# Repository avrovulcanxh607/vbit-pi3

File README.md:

# vbit-pi3
Teletext inserter board for the Raspberry Pi

Code available at https://github.com/peterkvt80/vbit-py<br>
Instructions and other details available at https://www.nathanmediaservices.co.uk/vbit-pi/

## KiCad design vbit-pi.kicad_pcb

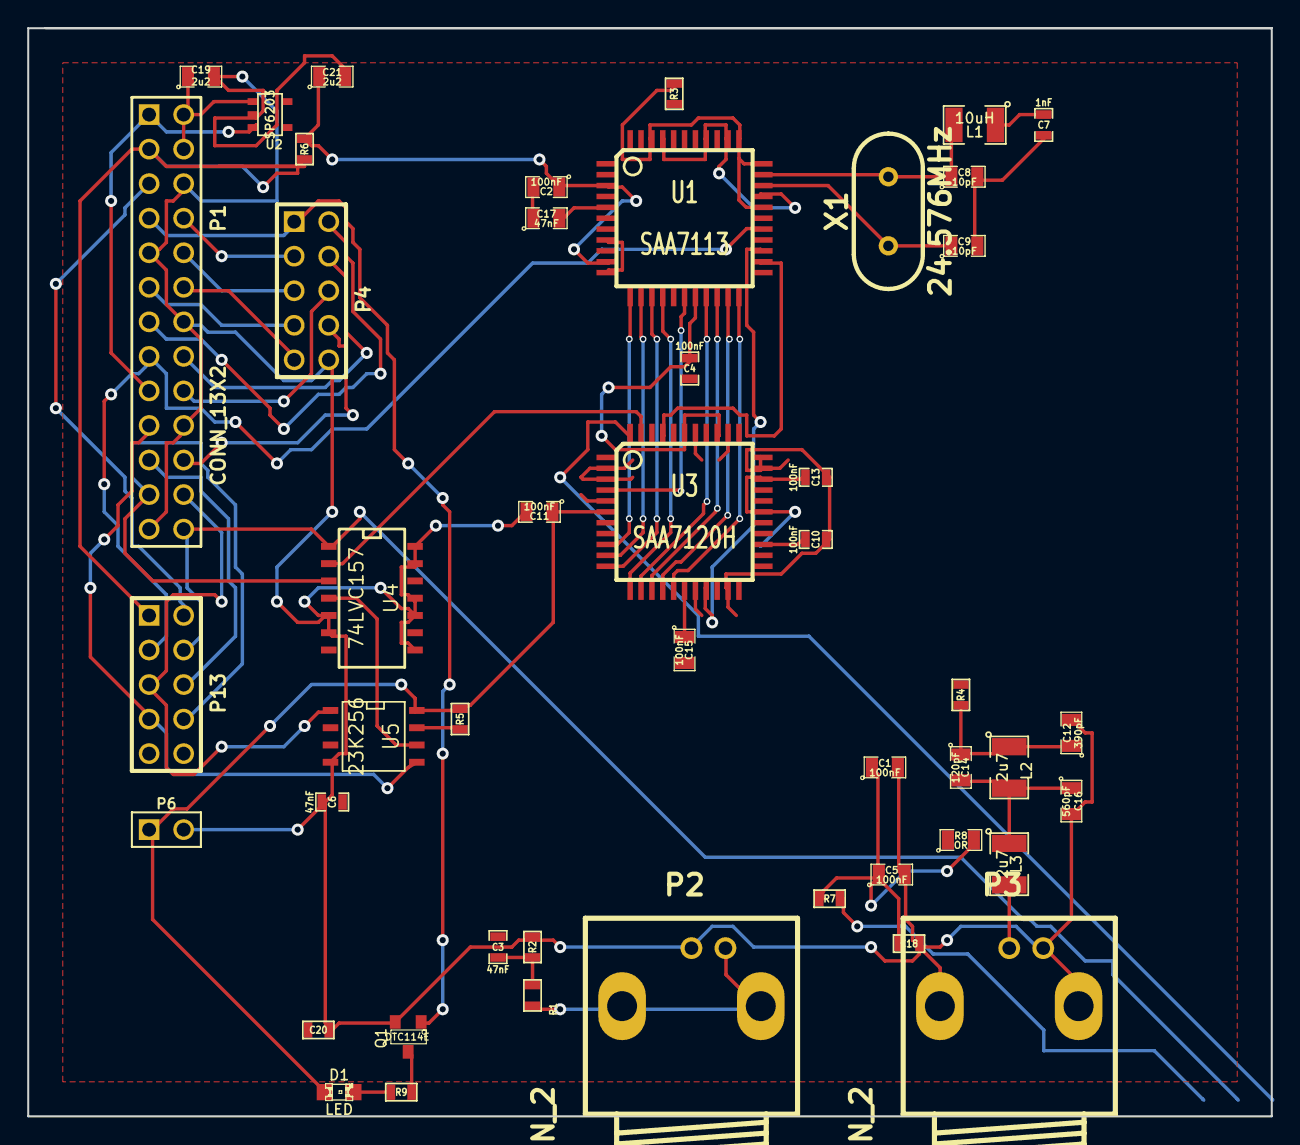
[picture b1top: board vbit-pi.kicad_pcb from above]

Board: 2 copper layers, 91.4 x 80.0 mm, 47 parts (0 on the bottom side), 51 nets.

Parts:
C1, C2, C5, C11, C15: 100nF; SM0805
C3, C6: 47nF; SM0603_Capa
C4, C10, C13: 100nF; SM0603_Capa
C7: 1nF; SM0603_Capa
C8, C9: 10pF; SM0805
C12: 390pF; SM0805
C14: 120pF; SM0805
C16: 560pF; SM0805
C17: 47nF; SM0805
C18: 100nF; SM0603
C19, C21: 2u2; SM0805
C20: 10nF; SM0603
D1: LED; LED-0805
L1: 10uH; SM1210
L2, L3: 2u7; SM1210
P1: CONN_13X2; pin_array_13x2
P2, P3: CONN_2; BNC_Socket_TYCO-AMP_RevA_Date21Jun2010
P4, P13: CONN_5X2; PIN_ARRAY_5x2
P6: CONN_2; PIN_ARRAY_2X1
Q1: DTC114E; SOT23
R1: 18R; SM0603
R2: 56R; SM0603
R3: 1k; SM0603
R4: 8R2; SM0603
R5: 47k; SM0603
R6, R7: 3k3; SM0603
R8: OR; SM0805
R9: 220R; SM0603
U1: SAA7113; TQFP44
U2: SP6203; SOT23-5
U3: SAA7120H; TQFP44
U4: 74LVC157; SO14N
U5: 23K256; SO8N
X1: 24.576MHz; HC-49V

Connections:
3V3 Power: P1.1, P1.17, U2.3
5V Power: C19.1, P1.2, P1.4, U2.1
+3.3V: C1.1, C2.1, C4.1, C5.1, C10.1, C11.1, C13.1, C15.1, C18.1, C21.1, D1.1, P6.1, R3.2, R5.1, R6.1, R7.1, R8.2, U1.3, U1.10, U1.18, U1.29, U1.33, U1.34, U1.42, U3.6, U3.17, U3.25, U3.28, U3.31, U3.36, U3.39, U3.40, U5.8
/DVID0: U1.22, U3.16
/DVID1: U1.21, U3.15
/DVID2: U1.20, U3.14
/DVID3: U1.19, U3.13
/DVID4: U1.15, U3.12
/DVID5: U1.14, U3.11
/DVID6: U1.13, U3.10
/DVID7: U1.12, U3.9
/LLC: U1.17, U3.4
/RTC: U1.25, U3.19
CSN: P1.24, P13.5, U5.1
FLD: P1.15, P13.3, U1.27
GND: C1.2, C2.2, C4.2, C5.2, C6.1, C7.2, C8.2, C9.2, C10.2, C11.2, C12.2, C13.2, C15.2, C16.2, C17.1, C18.2, C19.2, C20.2, C21.2, P1.6, P1.9, P1.14, P1.20, P1.25, P2.1, P3.2, P4.10, P6.2, Q1.2, R2.2, U1.2, U1.6, U1.8, U1.11, U1.16, U1.28, U1.30, U1.35, U1.37, U1.41, U2.2, U3.2, U3.3, U3.5, U3.18, U3.21, U3.32, U3.33, U3.35, U3.38, U4.5, U4.6, U4.8, U4.10, U4.11, U4.13, U4.14, U5.4
GPIO4: P1.7, P4.1, Q1.1
GPIO14: P1.8, P4.3
GPIO15: P1.10, P4.5
GPIO17: P1.11, P4.7
GPIO18: P1.12, P4.9
GPIO21: P1.13, P4.2
GPIO23: P1.16, P4.4
GPIO24: P1.18, P4.6
GPIO25: P1.22, P4.8
MISO: P1.21, P13.6, U3.44, U5.2
MOSI: P1.19, P13.7, U5.5
MUX: P1.26, P13.4, U4.1
unnamed: R4.1, U3.30
unnamed: U4.4, U5.6
unnamed: C3.2, U1.4
unnamed: R5.2, U5.7
unnamed: C20.1, U2.4
unnamed: R8.1, U2.5
unnamed: C17.2, U1.5
unnamed: D1.2, R9.2
unnamed: Q1.3, R9.1
unnamed: R3.1, U1.40
unnamed: C9.1, U1.31, X1.1
unnamed: L3.2, P3.1
unnamed: C6.2, U1.44
unnamed: C12.1, C14.1, L2.1, R4.2
unnamed: C14.2, C16.1, L2.2, L3.1
unnamed: C8.1, L1.2, U1.32, X1.2
unnamed: P2.2, R1.1
unnamed: C7.1, L1.1
unnamed: C3.1, R1.2, R2.1
SCL: P1.5, P13.2, R7.2, U1.24, U3.41
SCLK: P1.23, P13.8, U4.3
SDA: P1.3, P13.1, R6.2, U1.23, U3.42
TTXRQ: U3.43, U4.2

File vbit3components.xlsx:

QTY= | 10 | VBIT-Pi Kitting List |  |  |  |  | Excess
Description | QTY | Reference | Value | Style | Qty. | Bin | -Short | Supplier | Order Code
PCB | 1 | VBIT |  |  | 10 | 10 | 0 | JLCPCB
0603 SM CAP | 10 | C1 C2 C4 C5 C10 C11 C13 C15 C18 C22 | 100n | 0603 | 100 | 1 | -99 | FEC | 1907036
0603 SM CAP | 3 | C3 C6 C17 | 47n | 0603 | 30 | 5 | -25 | FEC | 8820007
0603 SM CAP | 1 | C7 | 1n | 0603 | 10 | 4 | -6 | FEC | 1414606
0603 SM CAP* | 2 | C8 C9 | 18pF | 0603 | 20 | 0 | -20 | FEC | 1865475
0603 SM CAP | 1 | C12 | 390pF | 0605 | 10 | 5 | -5 | FEC | 1414638
0603 SM CAP | 1 | C14 | 120pF | 0603 | 10 | 5 | -5 | FEC | 1414613
0603 SM CAP | 1 | C16 | 560pF | 0603 | 10 | 5 | -5 | FEC | 1828912
0805 SM CAP | 2 | C19 C21 | 2u2 | 603 | 20 | 0 | -20 | FEC | 9227830
0603 SM CAP | 1 | C20 | 10n | 0603 | 10 | 5 | -5 | FEC | 2070396
Yellow 0805 LED | 1 | D1 | Yellow | 0805 | 10 | 4 | -6 | FEC | 2099242
0805 SM INDUCTOR | 1 | L1 | 10uH | 0805 | 10 | 5 | -5 | FEC | 2112892
0603 SM INDUCTOR | 2 | L2,L3 | 2u7H | 0603 | 20 | 0 | -20 | FEC | 1669530
Header Socket | 1 | P1 | 20x2 | Pin 20x2 | 10 | 0 | -10 | FEC | 608-350
Right angle PCB RCA socket | 2 | P2 P3 |  | RCA | 20 | 0 | -20 | FEC
NPN digital Transistor SOT23 | 1 | Q1 | DTC143E | SOT23 | 10 | 5 | -5 | FEC | 8737274
0603 SM RESISTOR | 1 | R1 | 18R | 0603 | 10 | 5 | -5 | FEC | 9330747
0603 SM RESISTOR | 1 | R2 | 56R | 0603 | 10 | 5 | -5 | FEC | 9332197
0603 SM RESISTOR | 1 | R3 | 1k | 0603 | 10 | 5 | -5 | FEC | 9330380
0603 SM RESISTOR | 1 | R4 | 8R2 | 0603 | 10 | 5 | -5 | FEC | 2141558
0603 SM RESISTOR | 1 | R5 | 47k | 0603 | 10 | 5 | -5 | FEC | 9331255
0603 SM RESISTOR | 1 | R9 | 220R | 0603 | 10 | 5 | -5 | FEC | 2008352
SM IC SOT307-2 Video Processor | 1 | U1 | SAA7113H/V2 | TQFP44 | 10 | 10 | 0 | UTS
SM IC SOT23-5 Regulator 3V3 0.5A | 1 | U2 | SP6205 | SOT23-5 | 10 | 20 | 10 | FEC | 9388338
SM IC SOT307-2 Video encoder | 1 | U3 | SAA7121H | TQFP44 | 10 | 10 | 0 | UTS
SM IC Multiplexer | 1 | U4 | 74LVC157 | SOIC16 | 10 | 0 | -10 | FEC | 1103068
SM IC Serial SRAM | 1 | U5 | 23K256-I/SN | SOIC8 | 10 | 0 | -10 | FEC | 1695547
Crystal | 1 | X1 | 24.576MHz/18pF | HC49/S | 10 | 0 | -10 | FEC | 1611790
DNF = Do Not Fit. AVR version only
Prototyping board | 1 |  |  |  |  |  |  | FEC | 2295747

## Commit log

2019-03-17 fixed old order codes
2019-06-03 Made some design for manufacturability layout improvements, changed some footprints and updated BOM
